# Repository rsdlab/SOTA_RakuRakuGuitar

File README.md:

# 作品について　　

らくラクギターは誰でもかっこよく簡単に弾けるをコンセプトに開発されたギターである。　
　

マイコンはSONY製のSPRESENSEを使用している。　　

このらくラクギターには3種類のモードがある。　　

* ビギナーモード　ホイールを回すだけで演奏できるモード　　
* コードモード　弦を模したタッチセンサを1箇所もしくは2箇所押さえるだけで演奏できるモード　　
* マニュアルモード　本物のギターと同様に演奏できるモード　　

らくラクギターはM,m,7,sus4,dim,aug,M7,m7,7sus4に対応している。　　

らくラクギターの製作から実際に動かすまでの手順を以下に示す。　

1.　必要な部品の準備　　

2.　ギターのハード作成　　

3.　回路の作成　　

4.　動かすための準備　　

5.　らくラクギターの動かし方　

以下ではこれらを詳細に述べる。　　

 # 製作&動作手順　　
 ## 必要な部品の準備　　
下記の部品表の通りに各種部品を用意する。

## ギターのハード作成　　
こちらの動画を参考にギターを組み立てる。[youtubeへ移動](https://www.youtube.com/watch?v=TPaNkqSTSBw)　　
　　

表面の板を部品表にもあるベニヤ板で代替した。　　

タッチセンサやグランド線を通すためのスペースはギターのネックをノミや彫刻刀で彫る。　　

また、設計図を基に固定を行う。　　

 ## 回路の作成　　
下記の回路図の通りに部品をはんだづけし、回路を作成する。

※下のタッチセンサ制御基板の配線の図も見てください。

基板は[Elecrow](https://www.elecrow.com/)にてオーダメイドで発注したものである。

タッチセンサ制御部の基板データがPCB_data/touch_sensor_main、指版部の基板データがPCB_data/touch_sensor_touchとなっている。　　

 ## 動かすための準備　　
まずはSPRESENSEにプログラムを書き込む。  

SPRESENSEのセットアップを行う。詳しくは[こちら](https://developer.sony.com/develop/SPRESENSE/docs/arduino_set_up_ja.html)

書き込みはArduino IDEを用いる。ビルドも書き込みもメインコアからサブコア3まで1つづつしなければいけないので注意が必要である。メインコアへの書き込みはメモリを640KByteとすること。

次にSDカードに音源データを取り込む。SDカードにAとEのファイルを入れる。そしてSPRESENSEに差し込む。

回路やSPRESENSEの配線を完了させる。

SPRESENSEの配線とタッチセンサ制御基板の配線は以下の図の通りである。

そして設計図を基に裏板を固定する。　　

 ## らくラクギターの動かし方　　
まずは電源供給が必要である。　　

ギターからUSB(TypeA)が出ているのでモバイルバッテリーに接続する。

そしてらくラクギターにはスイッチが3つついており、モードを選択できる。

上から1つ目のスイッチを下、3つ目のスイッチを下にするとビギナーモードとなる。　　

上から1つ目のスイッチを下、3つ目のスイッチを上にするとコードモードとなる。

上から1つ目のスイッチを上にするとマニュアルモードとなる。　　

2つ目のスイッチを下にするとアコースティックギター、上にするとエレキギターの音が出せるようになる。　　

ギター裏についているボリュームを回すことで音量調整が可能である。(時計回りで音量が大きく、反時計回りで音量が小さくなる)　　

以下で各モードについて詳細に説明する。　　

共通事項として電源投入から一定時間経つとギターのジャーンと弾く音が勝手に再生される。これは準備完了の合図である。この合図があるまでホイールを回したり、タッチセンサを触ってはいけない。　　

ホイールの回転方向によってアップストロークとダウンストロークの切り替えが可能である。　　

 ### ビギナーモード　　
らくラクギターにPCから楽曲をとりこむ方法から説明する。　　

1. 楽曲を決定し、コード譜をテキストファイル(〇〇.txt)で作成する。　　
2. SPRESENSEに電源を投入する。
3. 楽曲を取り込む用のアプリケーション(rakuraku_guitar_gui.exe)を起動する。
4. 1にて作成したテキストファイルを選択する。　　
5. ジャーンという音がするまで待機し、音がなったらホイールを回すことでビギナーモードの演奏ができる。　　

注意点としては各コードは1ストローク分しか再生されない。なので、コードの変化するタイミングでホイールを回す必要がある。ただし、テキストファイルにコードを2回ずつ打つことで2ストロークづつにするなどテキストファイルの工夫である程度対応することは可能である。

ビギナーモードスイッチをOFFからONにするとコード譜の始めに戻る。　　

また、らくラクギターはコード(音)の変化にしか対応していないため,
タイミングについてはユーザーに完全に委ねられる。

 ### コードモード　　
1. SPRESENSEに電源を投入する。　　
2. ジャーンという音がするまで待機し、音がなったらコードモードの演奏ができる。タッチセンサを触りながらホイールを回すことで触っているセンサの位置に対応しているコードを鳴らすことができる。　　

コードの配置を以下に示す。

1フレット目はCに、12フレット目はBに対応している。

M7はMと7の同時押し、m7はmと7の同時押し、7sus4はsus4と7に同時押しで演奏ができる。　　

どこも触れないままホイールを回すと6弦全てを開放したときの音が鳴る。　　

注意点としてはタッチセンサを触れるときに同時にネック裏に通してあるグランド線も触らないといけない。そうしないとタッチセンサの値が正しく得られずコードがうまく鳴らせない。　　

また、コードの判定は、触れていると判定されているタッチセンサと完全一致することでコードが決定する。逆に言えば他の余計な部分を触っていると正しくコードが認識されない。コードのリストに該当しない押さえ方でホイールを回した場合は無音となる。　　

 ### マニュアルモード　　
1. SPRESENSEに電源を投入する。　　
2. ジャーンという音がするまで待機し、音がなったらマニュアルモードの演奏ができる。タッチセンサを触りながらホイールを回すことで触っているセンサの位置に対応しているコードを鳴らすことができる。　　

マニュアルモードの押さえ方はローコード1種+ハイコード1種、ローコードが存在しない場合はハイコード2種を搭載している。　　

具体的な押さえ方は[ギタコン](https://guitar-concierge.com/chord/)の各コードの見出しになっているコード2種を実装している。ローコードがあるのにも関わらず見出しにローコードが無いコードについてはローコード1種+見出しのハイコード2種の計3種を実装している。　　

どこも触れないままホイールを回すと6弦全てを開放したときの音が鳴る。　　

注意点としてはコードモード同様、タッチセンサを触れるときに同時にネック裏に通してあるグランド線も触らないといけない。そうしないとタッチセンサの値が正しく得られずコードがうまく鳴らせない。　　

また、コードの判定は、触れていると判定されているタッチセンサと完全一致することでコードが決定する。逆に言えば他の余計な部分を触っていると正しくコードが認識されない。コードのリストに該当しない押さえ方でホイールを回した場合は無音となる。　　

開放弦とミュートについては触れないように設定してある。特にミュートの弦に触れないように注意が必要である。

# リポジトリの構成　　

* program：SPRESENSEに書き込むプログラム

* library：SPRESENSEに必要なライブラリの追加データ。詳細は中のreadmeを参照

* rakuraku_guitar_gui：PCで使う楽曲を取り込む用のアプリケーションとそのプログラム

* PCB_data：自作した基板のデータ

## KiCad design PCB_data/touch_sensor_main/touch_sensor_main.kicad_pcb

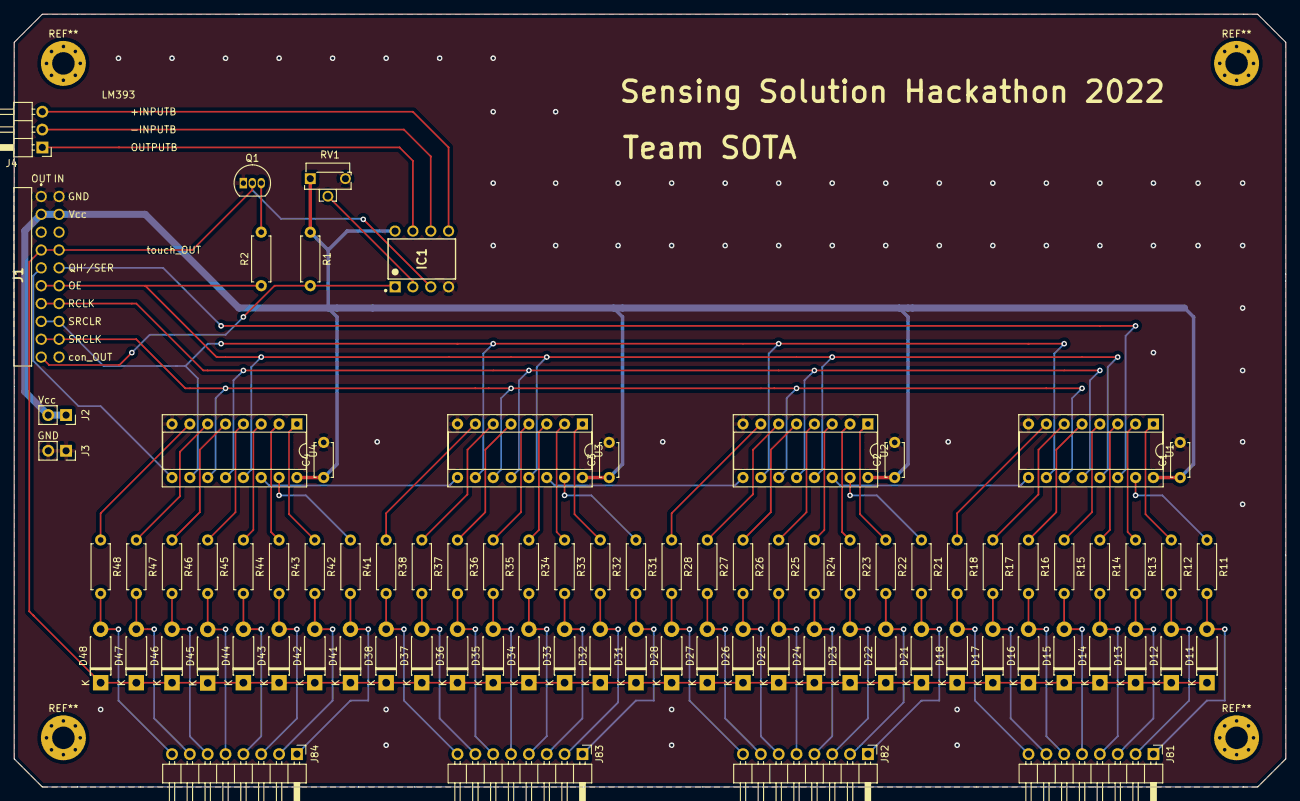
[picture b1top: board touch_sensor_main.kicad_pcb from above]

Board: 2 copper layers, 181.0 x 110.0 mm, 85 parts (0 on the bottom side), 82 nets.

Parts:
C1, C2, C3, C4: C; C_Disc_D4.7mm_W2.5mm_P5.00mm
D11, D12, D13, D14, D15, D16, D17, D18, D21, D22, D23, D24, D25, D26, D27, D28, D31, D32, D33, D34, D35, D36, D37, D38, D41, D42, D43, D44, D45, D46, D47, D48: D; D_DO-41_SOD81_P7.62mm_Horizontal
IC1: LM393NG; DIP794W56P254L959H533Q8B
J1: PH-2X10RG; PH2X10RG
J2, J3: Conn_01x02_Male; PinSocket_1x02_P2.54mm_Vertical
J4: Conn_01x03_Female; PinHeader_1x03_P2.54mm_Horizontal
J81, J82, J83, J84: Conn_01x08_Female; PinHeader_1x08_P2.54mm_Horizontal
Q1: 2SC1815; TO-92_Inline
R1: 3k; R_Axial_DIN0207_L6.3mm_D2.5mm_P7.62mm_Horizontal
R2, R11, R12, R13, R14, R15, R16, R17, R18, R21, R22, R23, R24, R25, R26, R27, R28, R31, R32, R33, R34, R35, R36, R37, R38, R41, R42, R43, R44, R45, R46, R47, R48: R; R_Axial_DIN0207_L6.3mm_D2.5mm_P7.62mm_Horizontal
RV1: R_POT; Potentiometer_Runtron_RM-063_Horizontal
U1, U2, U3, U4: 74HC595; DIP-16_W7.62mm_Socket

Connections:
+3V3: C1.1, C2.1, C3.1, C4.1, IC1.8, J1.3, J1.4, J2.1, J2.2, R1.1, RV1.1, U1.16, U2.16, U3.16, U4.16
GND: C1.2, C2.2, C3.2, C4.2, IC1.4, J1.1, J1.2, J3.1, J3.2, Q1.1, RV1.3, U1.8, U2.8, U3.8, U4.8
unnamed: D11.1, D12.1, D13.1, D14.1, D15.1, D16.1, D17.1, D18.1, D21.1, D22.1, D23.1, D24.1, D25.1, D26.1, D27.1, D28.1, D31.1, D32.1, D33.1, D34.1, D35.1, D36.1, D37.1, D38.1, D41.1, D42.1, D43.1, D44.1, D45.1, D46.1, D47.1, D48.1, IC1.3, J1.7, J1.8, Q1.2
unnamed: D11.2, J81.1, R11.2
unnamed: D12.2, J81.2, R12.2
unnamed: D13.2, J81.3, R13.2
unnamed: D14.2, J81.4, R14.2
unnamed: D15.2, J81.5, R15.2
unnamed: D16.2, J81.6, R16.2
unnamed: D17.2, J81.7, R17.2
unnamed: D18.2, J81.8, R18.2
unnamed: D21.2, J82.1, R21.2
unnamed: D22.2, J82.2, R22.2
unnamed: D23.2, J82.3, R23.2
unnamed: D24.2, J82.4, R24.2
unnamed: D25.2, J82.5, R25.2
unnamed: D26.2, J82.6, R26.2
unnamed: D27.2, J82.7, R27.2
unnamed: D28.2, J82.8, R28.2
unnamed: D31.2, J83.1, R31.2
unnamed: D32.2, J83.2, R32.2
unnamed: D33.2, J83.3, R33.2
unnamed: D34.2, J83.4, R34.2
unnamed: D35.2, J83.5, R35.2
unnamed: D36.2, J83.6, R36.2
unnamed: D37.2, J83.7, R37.2
unnamed: D38.2, J83.8, R38.2
unnamed: D41.2, J84.1, R41.2
unnamed: D42.2, J84.2, R42.2
unnamed: D43.2, J84.3, R43.2
unnamed: D44.2, J84.4, R44.2
unnamed: D45.2, J84.5, R45.2
unnamed: D46.2, J84.6, R46.2
unnamed: D47.2, J84.7, R47.2
unnamed: D48.2, J84.8, R48.2
unnamed: IC1.1, J1.19, R1.2
unnamed: IC1.2, RV1.2
unnamed: IC1.5, J4.3
unnamed: IC1.6, J4.2
unnamed: IC1.7, J4.1
unnamed: J1.9, U4.9
unnamed: J1.10, U1.14
unnamed: J1.11, J1.12, R2.1, U1.13, U2.13, U3.13, U4.13
unnamed: J1.13, J1.14, U1.12, U2.12, U3.12, U4.12
unnamed: J1.15, J1.16, U1.10, U2.10, U3.10, U4.10
unnamed: J1.17, J1.18, U1.11, U2.11, U3.11, U4.11
unnamed: Q1.3, R2.2
unnamed: R11.1, U1.15
unnamed: R12.1, U1.1
unnamed: R13.1, U1.2
unnamed: R14.1, U1.3
unnamed: R15.1, U1.4
unnamed: R16.1, U1.5
unnamed: R17.1, U1.6
unnamed: R18.1, U1.7
unnamed: R21.1, U2.15
unnamed: R22.1, U2.1
unnamed: R23.1, U2.2
unnamed: R24.1, U2.3
unnamed: R25.1, U2.4
unnamed: R26.1, U2.5
unnamed: R27.1, U2.6
unnamed: R28.1, U2.7
unnamed: R31.1, U3.15
unnamed: R32.1, U3.1
unnamed: R33.1, U3.2
unnamed: R34.1, U3.3
unnamed: R35.1, U3.4
unnamed: R36.1, U3.5
unnamed: R37.1, U3.6
unnamed: R38.1, U3.7
unnamed: R41.1, U4.15
unnamed: R42.1, U4.1
unnamed: R43.1, U4.2
unnamed: R44.1, U4.3
unnamed: R45.1, U4.4
unnamed: R46.1, U4.5
unnamed: R47.1, U4.6
unnamed: R48.1, U4.7
unnamed: U1.9, U2.14
unnamed: U2.9, U3.14
unnamed: U3.9, U4.14

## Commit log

2022-12-26 first upload
